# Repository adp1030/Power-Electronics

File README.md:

# Power-Electronics
Repo for my materials for Power Electronics Spring '24

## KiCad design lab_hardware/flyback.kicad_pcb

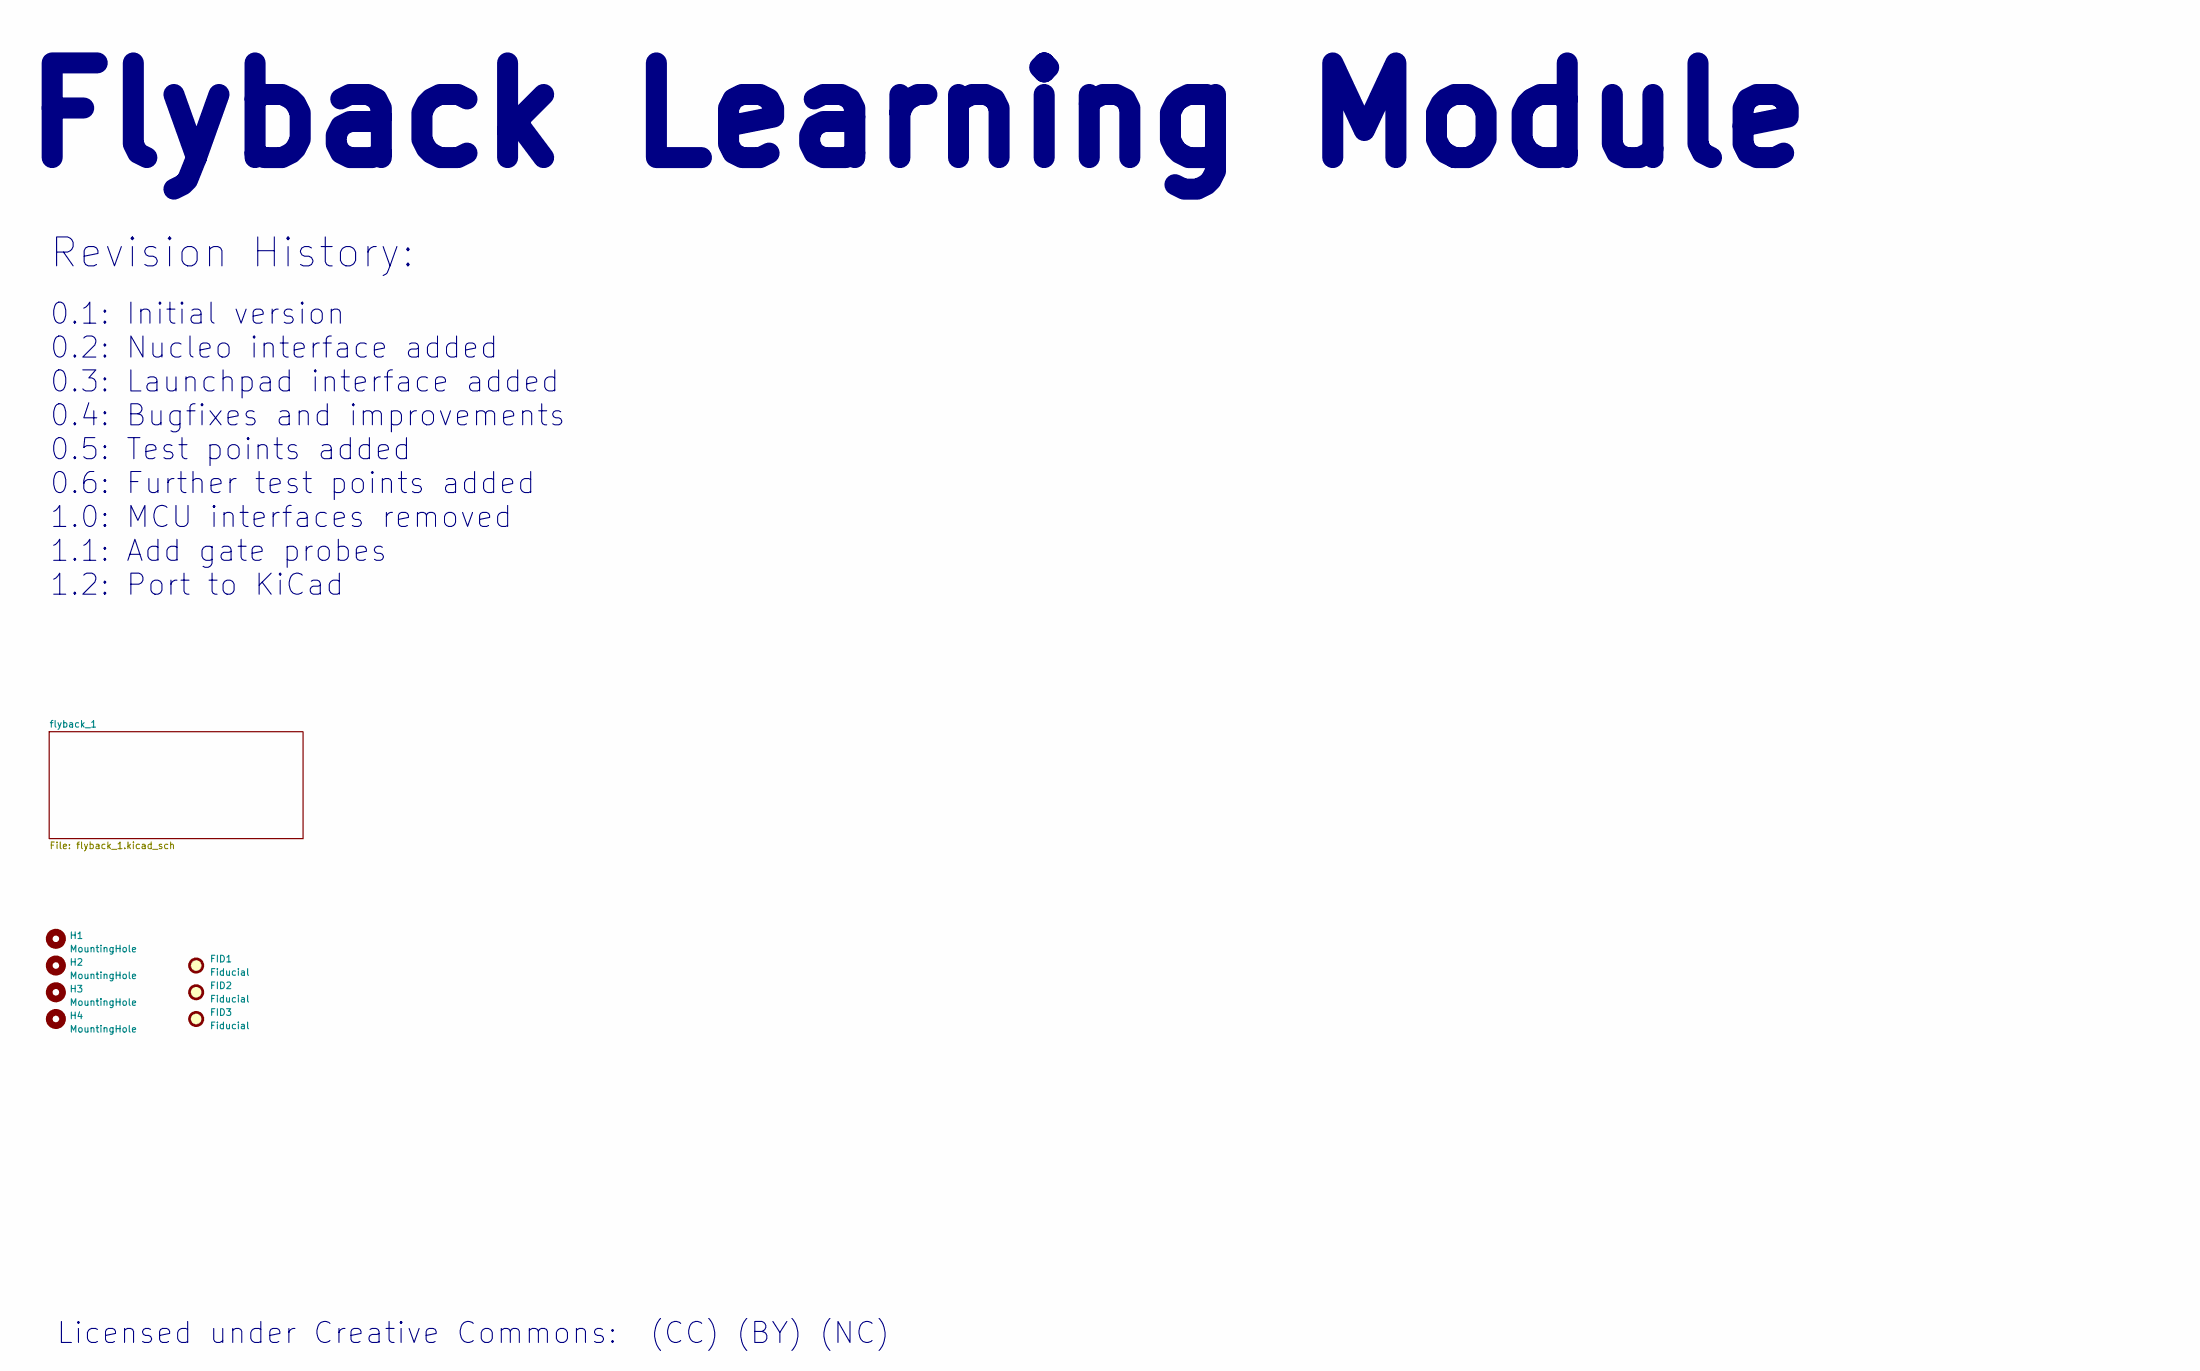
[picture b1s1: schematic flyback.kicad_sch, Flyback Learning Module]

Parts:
FID1, FID2, FID3: Fiducial; Fiducial_1mm_Mask3mm
H1, H2, H3, H4: MountingHole; MountingHole_2.5mm

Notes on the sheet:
0.1: Initial version 0.2: Nucleo interface added 0.3: Launchpad interface added 0.4: Bugfixes and improvements 0.5: Test points added 0.6: Further test points added 1.0: MCU interfaces removed 1.1: Add gate probes 1.2: Port to KiCad
Revision History:
Licensed under Creative Commons: (CC) (BY) (NC)
Flyback Learning Module

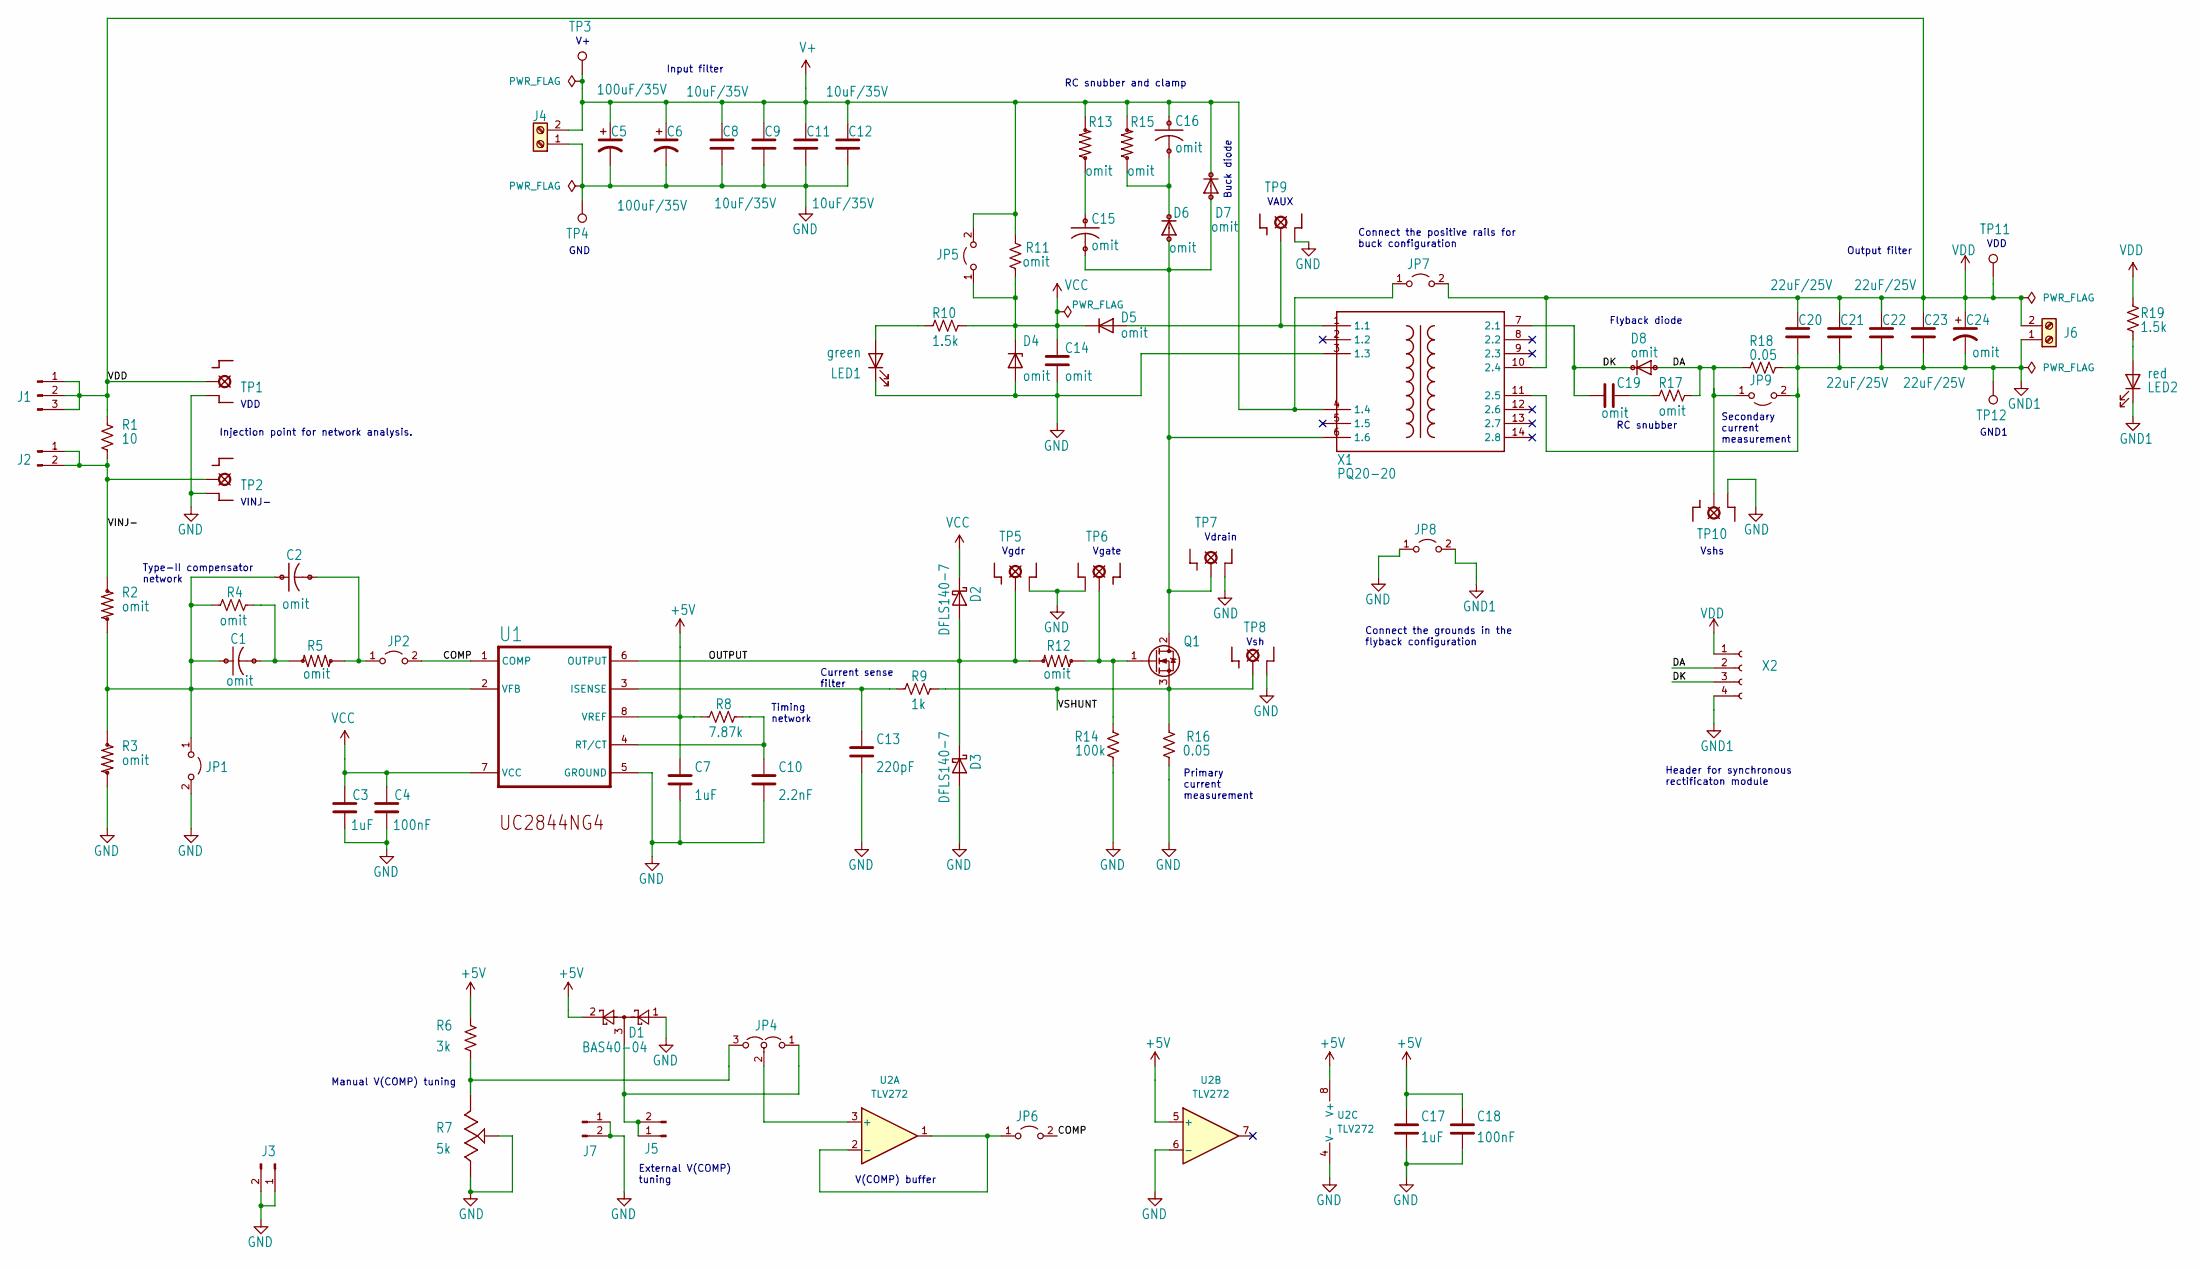
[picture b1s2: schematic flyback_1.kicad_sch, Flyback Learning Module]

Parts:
C1, C2: omit; C_PTH_0805
C3, C7, C17: 1uF; C_0805_2012Metric
C4, C18: 100nF; C_0805_2012Metric
C5, C6: 100uF/35V; CP_Radial_D8.0mm_P3.50mm
C8, C9, C11, C12: 10uF/35V; C_1210_3225Metric
C10: 2.2nF; C_0805_2012Metric
C13: 220pF; C_0805_2012Metric
C14: omit; C_1210_3225Metric
C15, C16: omit; C_PTH_200_MIL
C19: omit; C_0805_2012Metric
C20, C21, C22, C23: 22uF/25V; C_1210_3225Metric
C24: omit; CP_Radial_D8.0mm_P3.50mm
D1: BAS40-04; SOT-23
D2, D3: DFLS140-7; D_PowerDI-123
D4: omit; D_PowerDI-123
D5: omit; DIOM5226X240N
D6: omit; D_PTH_350_MIL
D7: omit; DIOM5226X240N_NOSMD_PTH
D8: omit; DIOM5226X240N_PTH
J1: JTP2E; PinHeader_1x03_P2.54mm_Vertical
J2, J3, J5: JTP1E; PinHeader_1x02_P2.54mm_Vertical
J4, J6: 691311500102; SHDR2W100P0X508_1X2_1216X850X1
J7: JP1E; PinHeader_1x02_P2.54mm_Vertical
JP1, JP2, JP5, JP6, JP7, JP8, JP9: JP1E; PinHeader_1x02_P2.54mm_Vertical
JP4: JP2E; PinHeader_1x03_P2.54mm_Vertical
LED1: green; D_0805_2012Metric
LED2: red; D_0805_2012Metric
Q1: IRF512SOCKETS; TO-220-3_PTH
R1: 10; R_0805_2012Metric
R2, R3, R5, R12: omit; R_PTH_0805
R4, R11, R17: omit; R_0805_2012Metric
R6: 3k; R_0805_2012Metric
R7: 5k; 63M_1
R8: 7.87k; R_0805_2012Metric
R9: 1k; R_0805_2012Metric
R10, R19: 1.5k; R_0805_2012Metric
R13, R15: omit; R_PTH_NOSMD
R14: 100k; R_0805_2012Metric
R16, R18: 0.05; R_2010_5025Metric
TP1, TP2, TP5, TP6, TP7, TP8, TP9, TP10: TPTEK; RIGOL_PROBE
TP3, TP4, TP11, TP12: TP_6021
U1: TEXAS_INSTRUMENTS_UC2844NG4TEXAS_INSTRUMENTS_UC28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; DIP-8_W7.62mm_Socket
U2: TLV272; SO-8_3.9x4.9mm_P1.27mm
X1: PQ20-20; CSV-PQ20-20
X2: omit; PinSocket_1x04_P2.54mm_Vertical

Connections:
+5V: C7.1, C17.1, C18.1, D1.2, R6.1, R8.2, U1.8 (VREF), U2.5 (+), U2.8 (V+)
/flyback_1/COMP: JP2.2 (B), JP6.2 (B), U1.1 (COMP)
/flyback_1/DA: D8.2 (A), JP9.1 (A), R17.1, R18.2, TP10.T (MP), X2.2
/flyback_1/DK: C19.1, D8.1 (C), X1.7 (2.1), X2.3
/flyback_1/N$15: C1.1, C2.1, JP1.1 (A), R2.2, R3.1, R4.2, U1.2 (VFB)
/flyback_1/OUTPUT: D2.2 (A), D3.1 (K), R12.2, TP5.T (MP), U1.6 (OUTPUT)
/flyback_1/VINJ-: J2.1, J2.2, R1.2, R2.1, TP2.T (MP)
/flyback_1/VSHUNT: Q1.3 (S), R9.1, R16.2, TP8.T (MP)
GND: C3.2, C4.2, C5.2, C6.2, C7.2, C8.2, C9.2, C10.2, C11.2, C12.2, C13.2, C14.2, C17.2, C18.2, D1.1, D3.2 (A), D4.2 (A), J3.1, J3.2, J4.1, J7.1, J7.2, JP1.2 (B), JP8.1 (A), LED1.1 (K), R3.2, R7.2 (S), R7.3 (E), R14.1, R16.1, TP1.G, TP2.G, TP4.1, TP5.G, TP6.G, TP7.G, TP8.G, TP9.G, TP10.G, U1.5 (GROUND), U2.4 (V-), U2.6 (-), X1.3 (1.3)
GND1: C20.2, C21.2, C22.2, C23.2, C24.2, J6.1, JP8.2 (B), JP9.2 (B), LED2.1 (K), R18.1, TP12.1, X1.11 (2.5), X2.4
unnamed: C1.2, R4.1, R5.2
unnamed: C15.1, R13.1
unnamed: C19.2, R17.2
unnamed: D5.2 (A), TP9.T (MP), X1.1 (1.1)
unnamed: C15.2, D6.2 (A), D7.2 (A), Q1.2 (D), TP7.T (MP), X1.6 (1.6)
unnamed: C16.2, D6.1 (C), R15.1
unnamed: D1.3, J5.1, J5.2, JP4.1 (A)
unnamed: C2.2, JP2.1 (A), R5.1
unnamed: JP4.3 (B), R6.2, R7.1 (A)
unnamed: JP4.2 (C), U2.3 (+)
unnamed: JP6.1 (A), U2.1, U2.2 (-)
unnamed: LED1.2 (A), R10.2
unnamed: LED2.2 (A), R19.2
unnamed: Q1.1 (G), R12.1, R14.2, TP6.T (MP)
unnamed: C13.1, R9.2, U1.3 (ISENSE)
unnamed: C10.1, R8.1, U1.4 (RT/CT)
VBUS: C5.1, C6.1, C8.1, C9.1, C11.1, C12.1, C16.1, D7.1 (C), J4.2, JP5.2 (B), JP7.1 (A), R11.2, R13.2, R15.2, TP3.1, X1.4 (1.4)
VCC: C3.1, C4.1, C14.1, D2.1 (K), D4.1 (K), D5.1 (K), JP5.1 (A), R10.1, R11.1, U1.7 (VCC)
VDD: C20.1, C21.1, C22.1, C23.1, C24.1, J1.1, J1.2, J1.3, J6.2, JP7.2 (B), R1.1, R19.1, TP1.T (MP), TP11.1, X1.10 (2.4), X2.1

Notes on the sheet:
RC snubber
V(COMP) buffer
Primary current measurement
Vgdr
Header for synchronous rectificaton module
VAUX
VINJ-
GND1
GND
Injection point for network analysis.
Type-II compensator network
VDD
Vsh
Input filter
Timing network
Secondary current measurement
Vshs
RC snubber and clamp
Manual V(COMP) tuning
Vgate
Connect the grounds in the flyback configuration
Vdrain
Flyback diode
Connect the positive rails for buck configuration
External V(COMP) tuning
Buck diode
Output filter
Current sense filter

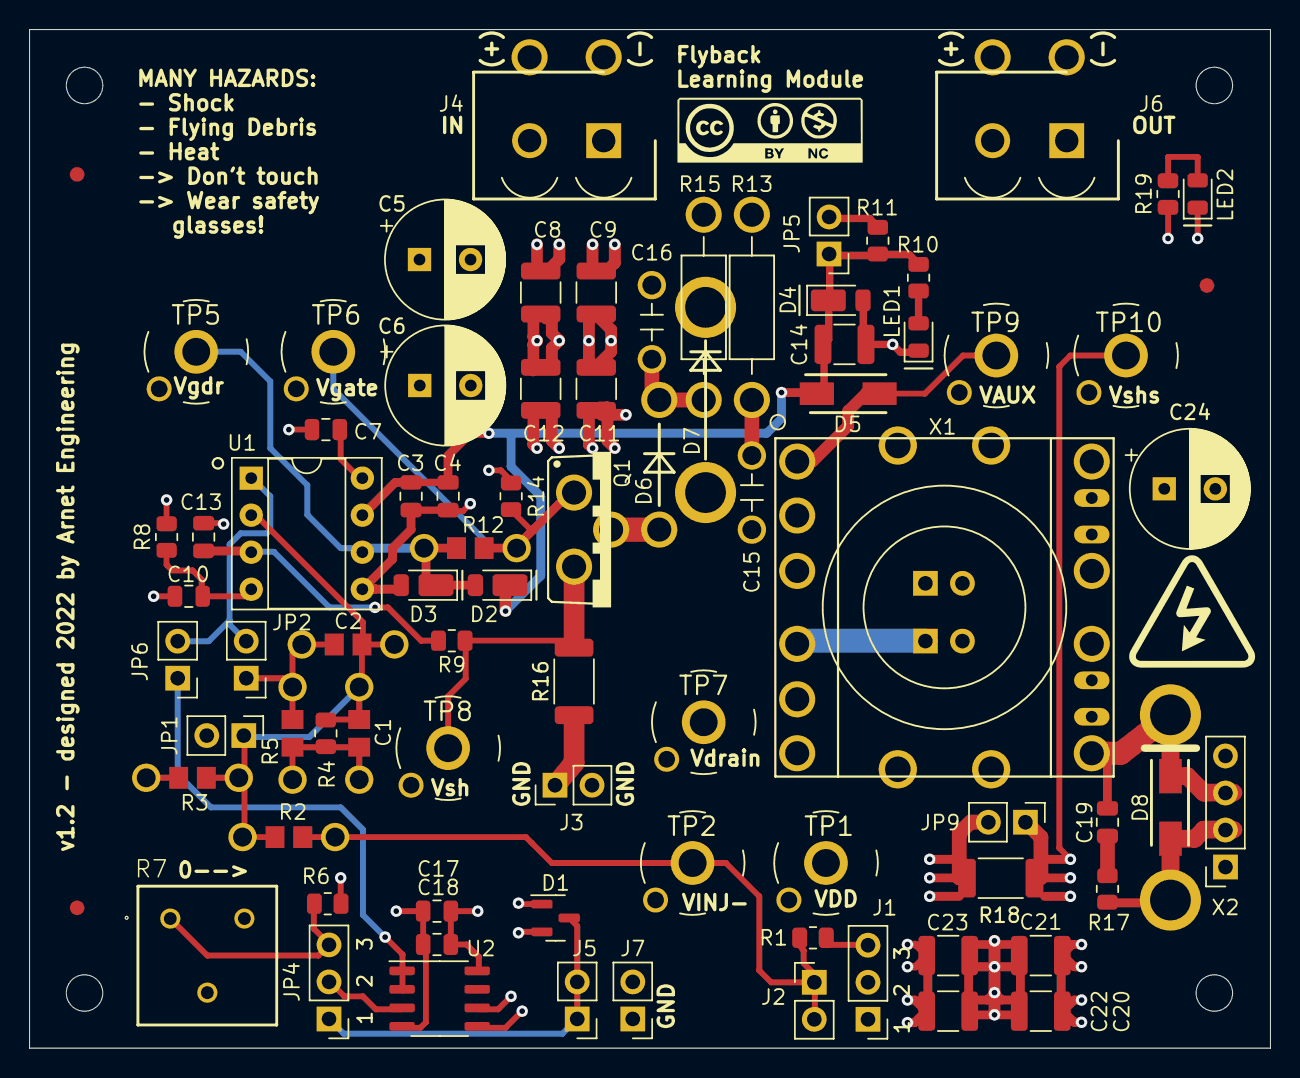
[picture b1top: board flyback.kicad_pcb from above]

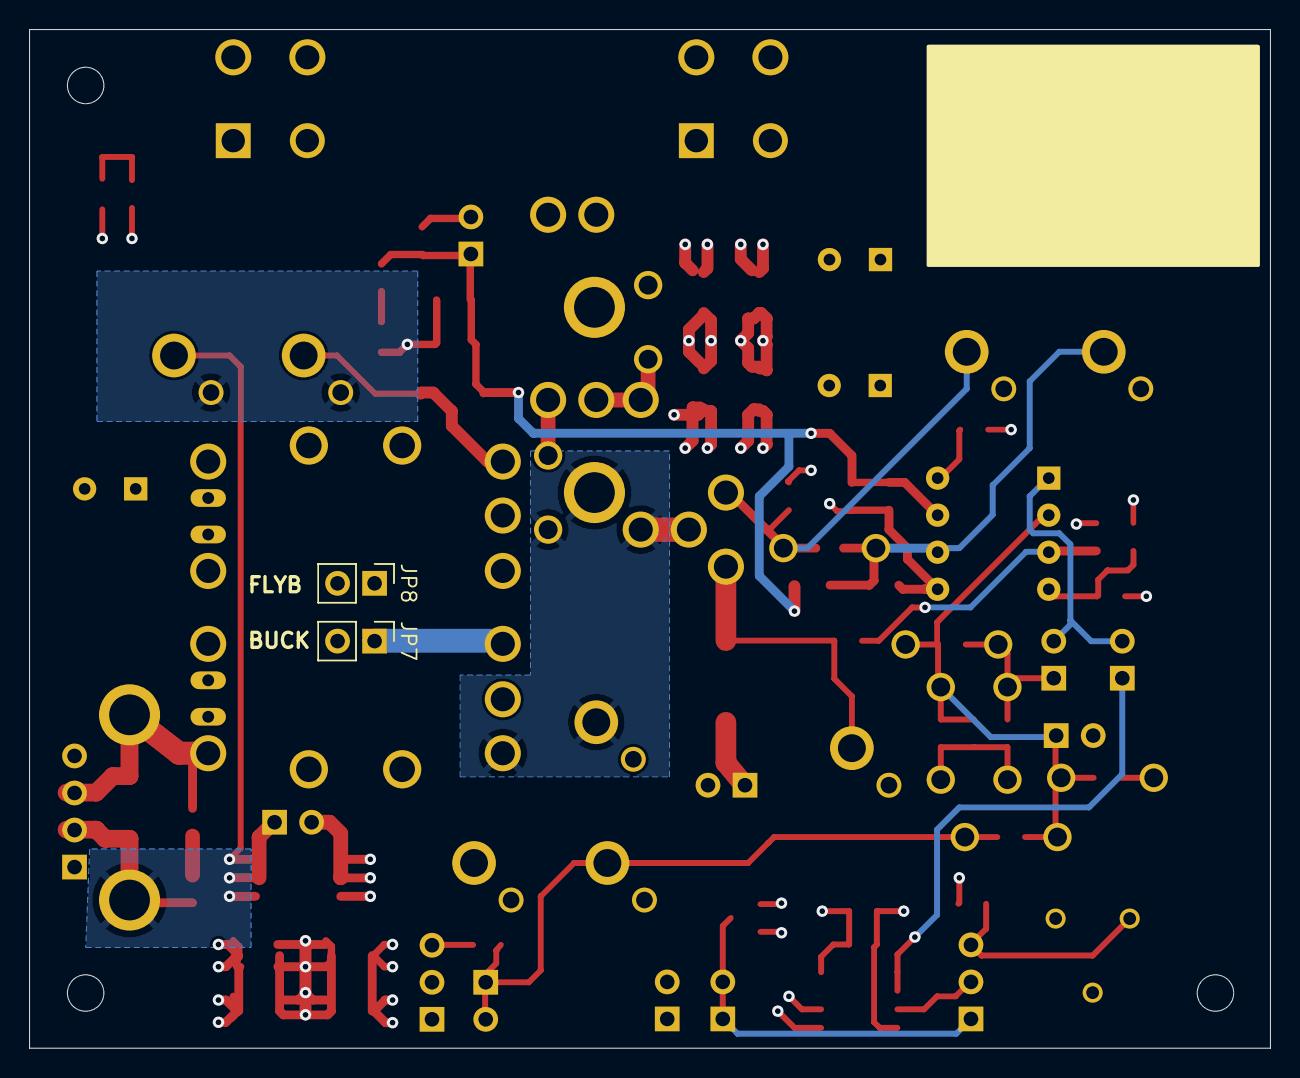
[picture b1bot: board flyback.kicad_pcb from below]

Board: 4 copper layers, 85.1 x 69.8 mm, 92 parts (2 on the bottom side), 29 nets.

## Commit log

2024-04-25 add all files up to lab 10
2024-05-01 adding lab 11 report and project files
2024-05-01 clean up project files and add README
2024-05-02 Adding project poster
2024-05-02 cleaning up old files
2024-05-02 add calculation notebook
